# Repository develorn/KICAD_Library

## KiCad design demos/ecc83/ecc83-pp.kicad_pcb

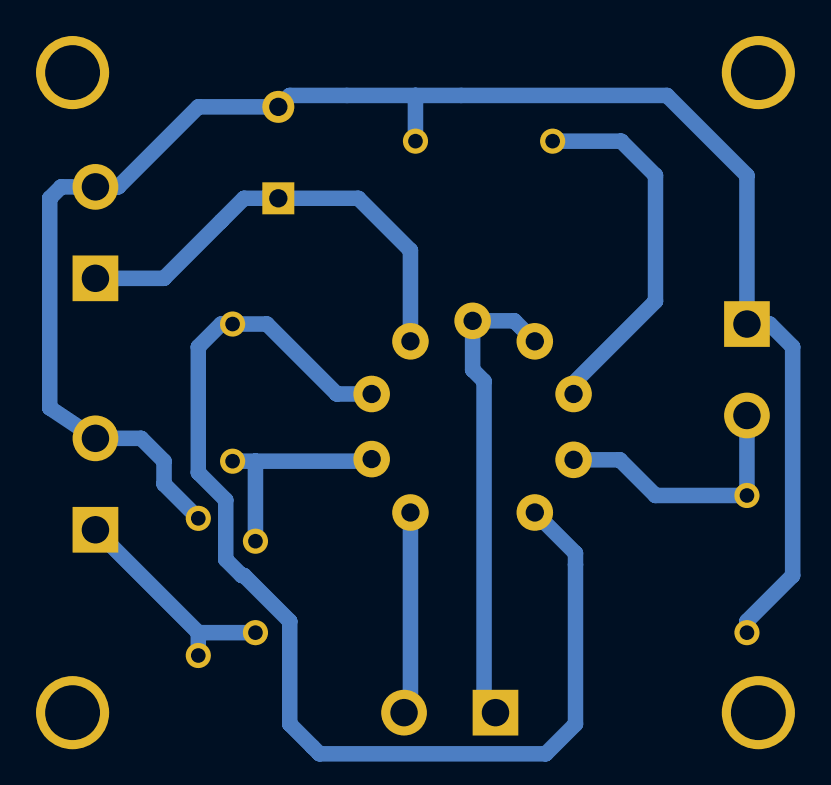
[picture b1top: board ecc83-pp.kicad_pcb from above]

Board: 2 copper layers, 15 parts (0 on the bottom side), 9 nets.

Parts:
1PIN, 1PIN#2, 1PIN#3, 1PIN#4: P***; 1pin
C1: 10uF; C2V10
C2: 680nF; C2
P1: IN; bornier2
P2: OUT; bornier2
P3: POWER; bornier2
P4: CONN_2; bornier2
R1, R2: 1.5K; R3
R3: 100K; R3
R4: 47K; R3
U1: ECC81_83; ECC-83-1

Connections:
GND: C1.2, P1.1, P2.2, P3.2, R2.2, R3.2, R4.2
unnamed: R1.1, U1.1, U1.7
unnamed: P4.2, U1.9
unnamed: P1.2, R4.1, U1.2
unnamed: R2.1, U1.3
unnamed: C2.1, P2.1, R3.1
unnamed: P4.1, U1.4, U1.5
unnamed: C1.1, P3.1, U1.6
unnamed: C2.2, R1.2, U1.8

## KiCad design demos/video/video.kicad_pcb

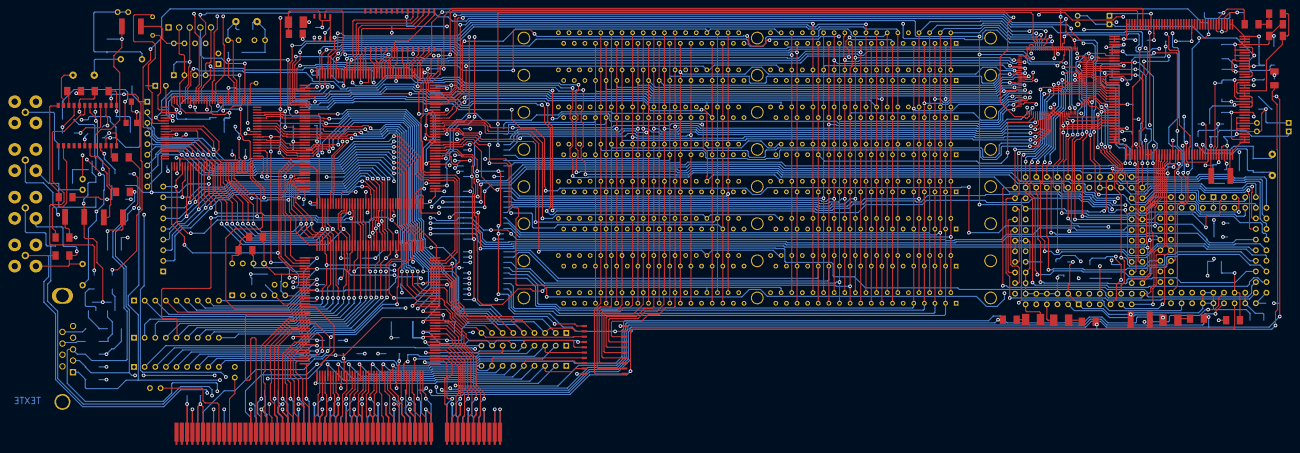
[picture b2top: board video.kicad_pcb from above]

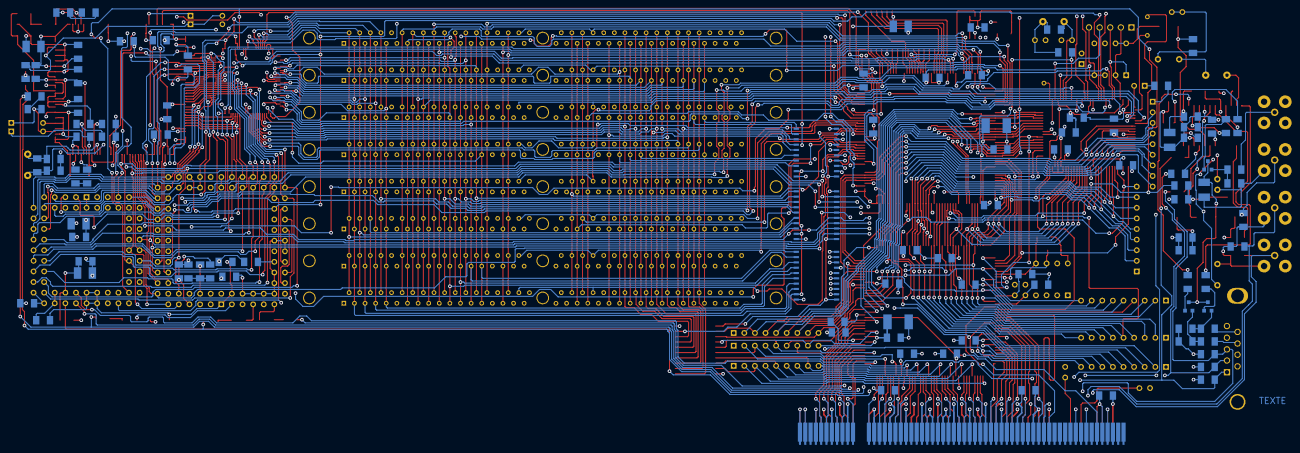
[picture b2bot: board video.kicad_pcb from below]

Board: 4 copper layers, 189 parts (103 on the bottom side), 371 nets.

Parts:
BUS1: BUSPCI_5V; BUSPCI
C1, C2, C3, C4, C5, C6, C7, C8, C9, C10, C11, C12, C13, C14, C15, C16, C17, C18, C19, C20, C21, C22, C23, C24, C25, C26, C27, C28, C29, C30, C31, C32, C33, C34, C35, C36, C70, C71, C72, C73: 100nF; SM1206
C37: 100pF; SM1206
C38, C56: 4,7uF; SM1812L
C39, C40, C41: 1uF; SM1210L
C42: 2,2uF; SM1210L
C43, C44, C45: 220nF; SM1206
C46, C47: 220pF; SM1206
C48: 22nF; SM1206
C49, C50: 22pF; C1
C51: 22uF; SM1210L
C52: 22uF; SM1206
C53: 330pF; SM1206
C54, C67, C68, C69: 4,7uF; SM1206
C55, C57: 4,7uF; SM1210L
C58, C59, C60, C61: 47nF; SM1206
C62, C63: 47uF; SM1210L
C64: 6,8uF; SM1210L
C65, C66: 22pF; SM1206
CV1: 5/30pF; CV3-30PF
D1, D2, D3, D4: BAT46; D3
D6: LED; LEDV
J4: DB9FEM; DB9FC
L1: 2,2uH; SM1812
L2, L3, L5: 22uH; SM1812
L4: 22uF; SM1812
L6: 470nS; LRTDK
P1, P2, P3, P8: BNC; SUBCLICK
P4: CONN_2; SIL-2
P5: CONN_5; PIN_ARRAY_5x1
P9, P10, P11: CONN_1; PINTST
P12: CONN_1; TESTPOINT
POT1: 100K; POT_CMS
Q1, Q2, Q3: BC848; SOT23EBC
R1: 10; SM1206
R2, R3: 100; SM1206
R4, R5, R6, R7, R48: 10K; SM1206
R8: 150; SM1206
R9: 150K; SM1206
R10, R11, R12, R13: 1K; SM1206
R14, R15: 1M; SM1206
R16, R17, R18, R19, R20, R21, R22, R23, R24: 220; SM1206
R25, R26: 220K; SM1206
R27: 27K; SM1206
R28, R29: 2,2K; SM1206
R30: 3,3K; SM1206
R31, R32, R33, R34, R35, R36: 470; SM1206
R37, R38: 510; SM1206
R39, R40, R41: 68; SM1206
R42, R43, R44, R45, R46, R47: 75; SM1206
RR1, RR2, RR3, RR6, RR8: 8x10K; SIL-9
RR4, RR5, RR7: 8x10K; r_pack8
U1: 24C16; 8dip300
U2: 4C4001; SO28
U3, U4, U5, U6: 74LS245; SO20L
U7: AV9173; SO8E
U8: BT253; PLCC84
U9: BT473; PLCC68
U10: BT812; PQFP160
U11: S5933_PQ160; PQFP160
U12, U13, U14, U15, U16, U17, U18, U19: SIM4X32; SIM72
U20: TDA8501; SO24E
U21: XC1736APD8; 8dip300
U22: XC4003-VQ100; VQFP100
U23: XC4003/PQ100; PQFP100
U24: XC4005-PQ160; PQFP160
W1: 16/32; SM1206
W2: FLOAT#; C1
W3: SERNV; C1
W4, W5: TEST; C1
X1: 10MHz; HC-18UV
X2: 30MHz; HC-18UV
X3: 4,433618MH; HC-18UH

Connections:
+3.3V: BUS1.A21, BUS1.A27, BUS1.A33, BUS1.A39, BUS1.A45, BUS1.A53, BUS1.B25, BUS1.B31, BUS1.B36, BUS1.B41, BUS1.B43, BUS1.B54, C68.1, C69.1
+5F: C55.1, L3.2, Q1.3, Q2.3, Q3.3
+5V: BUS1.A5, BUS1.A8, BUS1.A10, BUS1.A16, BUS1.A59, BUS1.A61, BUS1.A62, BUS1.B5, BUS1.B6, BUS1.B19, BUS1.B59, BUS1.B61, BUS1.B62, C9.1, C10.1, C11.1, C15.1, C17.1, C18.1, C19.1, C20.1, C21.1, C22.1, C24.1, C25.1, C26.1, C27.1, C28.1, C29.1, C30.1, C31.1, C38.1, C56.1, C57.1, C67.1, C70.1, C71.1, C72.1, C73.1, D2.2, D4.2, L2.1, L3.1, L4.1, L5.1, R1.2, R4.2, R5.2, R6.2, R7.2, R13.1, R28.1, R29.1, R48.1, RR1.1, RR2.1, RR3.1, RR4.1, RR5.1, RR6.1, RR7.1, RR8.1, U1.7, U1.8, U2.10, U3.20, U4.20, U5.20, U6.20, U10.31, U10.45, U10.57, U10.76, U10.91, U10.102, U10.112, U11.11, U11.31, U11.51, U11.71, U11.91, U11.111, U11.131, U11.151, U12.10, U12.30, U12.59, U13.10, U13.30, U13.59, U14.10, U14.30, U14.59, U15.10, U15.30, U15.59, U16.10, U16.30, U16.59, U17.10, U17.30, U17.59, U18.10, U18.30, U18.59, U19.10, U19.30, U19.59, U21.7, U21.8, U22.12, U22.22, U22.24, U22.25, U22.26, U22.37, U22.51, U22.63, U22.75, U22.89, U22.100, U23.3, U23.15, U23.28, U23.40, U23.54, U23.66, U23.78, U23.92, U24.20, U24.38, U24.40, U24.41, U24.42, U24.60, U24.81, U24.100, U24.120, U24.142, U24.160
/ESVIDEO-RVB/BLUE: C60.2, J4.3, R44.2, U9.39
/ESVIDEO-RVB/BLUE_IN: P3.1, R22.1, R46.1
/ESVIDEO-RVB/DPC0: RR7.2, U3.2, U8.16, U9.14, U10.92, U11.100, U23.13, U24.21
/ESVIDEO-RVB/DPC1: RR7.3, U3.3, U8.15, U9.15, U10.93, U11.99, U23.12, U24.22
/ESVIDEO-RVB/DPC2: RR7.4, U3.4, U8.14, U9.16, U10.94, U11.98, U23.11, U24.23
/ESVIDEO-RVB/DPC4: RR7.6, U3.6, U8.12, U9.18, U10.96, U11.95, U23.9, U24.25
/ESVIDEO-RVB/DPC5: RR7.7, U3.7, U8.11, U9.19, U10.97, U11.94, U23.8, U24.26
/ESVIDEO-RVB/DPC7: RR7.9, U3.9, U8.9, U9.21, U10.100, U11.88, U23.5, U24.28
/ESVIDEO-RVB/GREEN: C59.2, J4.2, R43.2, U9.38
/ESVIDEO-RVB/GREEN_IN: C3.2, P2.1, R23.1, R45.1
/ESVIDEO-RVB/OE_RVB-: U8.57, U9.29
/ESVIDEO-RVB/PCA0: U8.17, U9.24, U10.84, U23.65
/ESVIDEO-RVB/PCA2: U8.19, U9.26, U23.63
/ESVIDEO-RVB/RDCDA-: U9.22, U23.72
/ESVIDEO-RVB/REF+: R37.2, U8.64, U8.65, U8.66, U8.71, U8.73, U8.76, U8.78, U8.80, U8.82
/ESVIDEO-RVB/TVB2: U8.30, U9.63, U10.53, U22.94
/ESVIDEO-RVB/TVB3: U8.29, U9.64, U10.52, U22.95
/ESVIDEO-RVB/TVG0: U8.48, U9.53, U10.74, U22.67
/ESVIDEO-RVB/TVG1: U8.47, U9.54, U10.73, U22.68
/ESVIDEO-RVB/TVG2: U8.46, U9.55, U10.72, U22.69
/ESVIDEO-RVB/TVG3: U8.45, U9.56, U10.71, U22.70
/ESVIDEO-RVB/TVG4: U8.36, U9.57, U10.70, U22.71
/ESVIDEO-RVB/TVG5: U8.35, U9.58, U10.69, U22.78
/ESVIDEO-RVB/TVR0: U8.56, U9.45, U10.65, U22.82
/ESVIDEO-RVB/TVR1: U8.55, U9.46, U10.64, U22.83
/ESVIDEO-RVB/TVR2: U8.54, U9.47, U10.63, U22.84
/ESVIDEO-RVB/TVR5: U8.51, U9.50, U10.60, U22.87
/ESVIDEO-RVB/TVR6: U8.50, U9.51, U10.59, U22.90
/ESVIDEO-RVB/TVR7: U8.49, U9.52, U10.58, U22.91
/ESVIDEO-RVB/VAA: C33.1, C34.1, C35.1, C42.1, C51.1, C52.1, L5.2, U8.1, U8.43, U8.44, U8.84, U9.1, U9.2, U9.33, U9.34, U9.35, U9.36
/RAMS/CAS0-: U12.40, U13.40, U14.40, U15.40, U16.40, U17.40, U18.40, U19.40, U24.57
/RAMS/CAS2-: U12.42, U13.42, U14.42, U15.42, U16.42, U17.42, U18.42, U19.42, U24.59
/RAMS/CAS3-: U12.43, U13.43, U14.43, U15.43, U16.43, U17.43, U18.43, U19.43, U24.62
/RAMS/MXA0: U12.12, U13.12, U14.12, U15.12, U16.12, U17.12, U18.12, U19.12, U24.128
/RAMS/MXA1: U12.13, U13.13, U14.13, U15.13, U16.13, U17.13, U18.13, U19.13, U24.127
/RAMS/MXA2: U12.14, U13.14, U14.14, U15.14, U16.14, U17.14, U18.14, U19.14, U24.126
/RAMS/MXA3: U12.15, U13.15, U14.15, U15.15, U16.15, U17.15, U18.15, U19.15, U24.125
/RAMS/MXA4: U12.16, U13.16, U14.16, U15.16, U16.16, U17.16, U18.16, U19.16, U24.124
/RAMS/MXA5: U12.17, U13.17, U14.17, U15.17, U16.17, U17.17, U18.17, U19.17, U24.123
/RAMS/MXA6: U12.18, U13.18, U14.18, U15.18, U16.18, U17.18, U18.18, U19.18, U24.116
/RAMS/MXA7: U12.28, U13.28, U14.28, U15.28, U16.28, U17.28, U18.28, U19.28, U24.115
/RAMS/MXA8: U12.31, U13.31, U14.31, U15.31, U16.31, U17.31, U18.31, U19.31, U24.114
/RAMS/MXA9: U12.32, U13.32, U14.32, U15.32, U16.32, U17.32, U18.32, U19.32, U24.113
/RAMS/MXA10: U12.19, U13.19, U14.19, U15.19, U16.19, U17.19, U18.19, U19.19, U24.109
/RAMS/RAS3-: U15.34, U15.44, U24.68
/RAMS/RAS5-: U12.34, U12.44, U24.66
/RAMS/TVRAM0: U3.18, U12.2, U13.2, U14.2, U15.2, U16.2, U17.2, U18.2, U19.2, U22.17
/RAMS/TVRAM1: U3.17, U12.4, U13.4, U14.4, U15.4, U16.4, U17.4, U18.4, U19.4, U22.19
/RAMS/TVRAM2: U3.16, U12.6, U13.6, U14.6, U15.6, U16.6, U17.6, U18.6, U19.6, U22.20
/RAMS/TVRAM3: U3.15, U12.8, U13.8, U14.8, U15.8, U16.8, U17.8, U18.8, U19.8, U22.18
/RAMS/TVRAM4: U3.14, U12.20, U13.20, U14.20, U15.20, U16.20, U17.20, U18.20, U19.20, U22.28
/RAMS/TVRAM5: U3.13, U12.22, U13.22, U14.22, U15.22, U16.22, U17.22, U18.22, U19.22, U22.29
/RAMS/TVRAM6: U3.12, U12.24, U13.24, U14.24, U15.24, U16.24, U17.24, U18.24, U19.24, U22.31
/RAMS/TVRAM7: U3.11, U12.26, U13.26, U14.26, U15.26, U16.26, U17.26, U18.26, U19.26, U22.32
/RAMS/TVRAM8: U4.18, U12.49, U13.49, U14.49, U15.49, U16.49, U17.49, U18.49, U19.49, U22.33
/RAMS/TVRAM9: U4.17, U12.51, U13.51, U14.51, U15.51, U16.51, U17.51, U18.51, U19.51, U22.34
/RAMS/TVRAM10: U4.16, U12.53, U13.53, U14.53, U15.53, U16.53, U17.53, U18.53, U19.53, U22.35
/RAMS/TVRAM11: U4.15, U12.55, U13.55, U14.55, U15.55, U16.55, U17.55, U18.55, U19.55, U22.36
/RAMS/TVRAM12: U4.14, U12.57, U13.57, U14.57, U15.57, U16.57, U17.57, U18.57, U19.57, U22.39
/RAMS/TVRAM13: U4.13, U12.61, U13.61, U14.61, U15.61, U16.61, U17.61, U18.61, U19.61, U22.40
/RAMS/TVRAM14: U4.12, U12.63, U13.63, U14.63, U15.63, U16.63, U17.63, U18.63, U19.63, U22.41
/RAMS/TVRAM15: U4.11, U12.65, U13.65, U14.65, U15.65, U16.65, U17.65, U18.65, U19.65, U22.42
/RAMS/TVRAM16: U5.18, U12.3, U13.3, U14.3, U15.3, U16.3, U17.3, U18.3, U19.3, U22.43
/RAMS/TVRAM17: U5.17, U12.5, U13.5, U14.5, U15.5, U16.5, U17.5, U18.5, U19.5, U22.44
/RAMS/TVRAM18: U5.16, U12.7, U13.7, U14.7, U15.7, U16.7, U17.7, U18.7, U19.7, U22.45
/RAMS/TVRAM19: U5.15, U12.9, U13.9, U14.9, U15.9, U16.9, U17.9, U18.9, U19.9, U22.46
/RAMS/TVRAM20: U5.14, U12.21, U13.21, U14.21, U15.21, U16.21, U17.21, U18.21, U19.21, U22.47
/RAMS/TVRAM21: U5.13, U12.23, U13.23, U14.23, U15.23, U16.23, U17.23, U18.23, U19.23, U22.48
/RAMS/TVRAM22: U5.12, U12.25, U13.25, U14.25, U15.25, U16.25, U17.25, U18.25, U19.25, U22.53
/RAMS/TVRAM23: U5.11, U12.27, U13.27, U14.27, U15.27, U16.27, U17.27, U18.27, U19.27, U22.54
/RAMS/TVRAM24: U6.18, U12.50, U13.50, U14.50, U15.50, U16.50, U17.50, U18.50, U19.50, U22.55
/RAMS/TVRAM25: U6.17, U12.52, U13.52, U14.52, U15.52, U16.52, U17.52, U18.52, U19.52, U22.56
/RAMS/TVRAM26: U6.16, U12.54, U13.54, U14.54, U15.54, U16.54, U17.54, U18.54, U19.54, U22.57
/RAMS/TVRAM27: U6.15, U12.56, U13.56, U14.56, U15.56, U16.56, U17.56, U18.56, U19.56, U22.58
/RAMS/TVRAM28: U6.14, U12.58, U13.58, U14.58, U15.58, U16.58, U17.58, U18.58, U19.58, U22.59
/RAMS/TVRAM29: U6.13, U12.60, U13.60, U14.60, U15.60, U16.60, U17.60, U18.60, U19.60, U22.60
/RAMS/TVRAM30: U6.12, U12.62, U13.62, U14.62, U15.62, U16.62, U17.62, U18.62, U19.62, U22.61
/RAMS/TVRAM31: U6.11, U12.64, U13.64, U14.64, U15.64, U16.64, U17.64, U18.64, U19.64, U22.62
/RAMS/WRAM-: U12.47, U13.47, U14.47, U15.47, U16.47, U17.47, U18.47, U19.47, U24.63
/buspci.sch/ADR6: U11.132, U23.39, U24.143
/buspci.sch/BPCLK: U11.140, U23.30
/buspci.sch/EA1: RR2.6, U11.61
/buspci.sch/EA2: RR3.8, U11.69
/buspci.sch/EA3: RR3.6, U11.73
/buspci.sch/EA4: RR3.2, U11.81
/buspci.sch/EA5: RR4.4, U11.89
/buspci.sch/EA6: RR4.2, U11.97
/buspci.sch/EA7: RR5.9, U11.101
/buspci.sch/EA9: RR5.3, U11.113
/buspci.sch/EA10: RR6.9, U11.121
/buspci.sch/EA11: RR6.7, U11.129
/buspci.sch/EA12: RR6.5, U11.137
/buspci.sch/EA13: RR6.4, U11.141
/buspci.sch/EA14: RR4.8, U11.149
/buspci.sch/EA15: RR4.6, U11.153
/buspci.sch/EQ0: RR1.2, U11.1
/buspci.sch/EQ1: RR1.4, U11.9
/buspci.sch/EQ2: RR1.6, U11.17
/buspci.sch/EQ3: RR1.7, U11.21
/buspci.sch/EQ4: RR1.9, U11.29
/buspci.sch/EQ5: RR2.4, U11.33
/buspci.sch/EQ6: RR2.2, U11.41
/buspci.sch/EQ7: RR2.9, U11.49
/buspci.sch/PTATN-: RR5.2, U11.114, U23.18, U24.4
/buspci.sch/PTBE-1: U11.118, U23.21, U24.157
/buspci.sch/PTNUM0: U11.123, U23.34, U24.150
/buspci.sch/PTRDY-: RR6.2, U11.115, U23.19, U24.3
/buspci.sch/P_AD0: BUS1.A58, U11.56
/buspci.sch/P_AD1: BUS1.B58, U11.55
/buspci.sch/P_AD2: BUS1.A57, U11.54
/buspci.sch/P_AD3: BUS1.B56, U11.52
/buspci.sch/P_AD4: BUS1.A55, U11.48
/buspci.sch/P_AD5: BUS1.B55, U11.47
/buspci.sch/P_AD6: BUS1.A54, U11.46
/buspci.sch/P_AD7: BUS1.B53, U11.44
/buspci.sch/P_AD8: BUS1.B52, U11.42
/buspci.sch/P_AD9: BUS1.A49, U11.40
/buspci.sch/P_AD10: BUS1.B48, U11.39
/buspci.sch/P_AD11: BUS1.A47, U11.38
/buspci.sch/P_AD12: BUS1.B47, U11.36
/buspci.sch/P_AD13: BUS1.A46, U11.35
/buspci.sch/P_AD14: BUS1.B45, U11.34
/buspci.sch/P_AD15: BUS1.A44, U11.32
/buspci.sch/P_AD16: BUS1.A32, U11.14
/buspci.sch/P_AD17: BUS1.B32, U11.12
/buspci.sch/P_AD18: BUS1.A31, U11.8
/buspci.sch/P_AD19: BUS1.B30, U11.7
/buspci.sch/P_AD20: BUS1.A29, U11.6
/buspci.sch/P_AD21: BUS1.B29, U11.4
/buspci.sch/P_AD22: BUS1.A28, U11.3
/buspci.sch/P_AD23: BUS1.B27, U11.2
/buspci.sch/P_AD24: BUS1.A25, U11.158
/buspci.sch/P_AD25: BUS1.B24, U11.156
/buspci.sch/P_AD26: BUS1.A23, U11.155
/buspci.sch/P_AD27: BUS1.B23, U11.154
/buspci.sch/P_AD28: BUS1.A22, U11.152
/buspci.sch/P_AD29: BUS1.B21, U11.148
/buspci.sch/P_AD30: BUS1.A20, U11.147
/buspci.sch/P_AD31: BUS1.B20, U11.146
/buspci.sch/P_C/BE0#: BUS1.A52, U11.43
/buspci.sch/P_C/BE1#: BUS1.B44, U11.28
/buspci.sch/P_C/BE2#: BUS1.B33, U11.15
/buspci.sch/P_C/BE3#: BUS1.B26, U11.159
/buspci.sch/P_CLK: BUS1.B16, U11.142
/buspci.sch/P_DEVSEL#: BUS1.B37, U11.20
/buspci.sch/P_FRAME#: BUS1.A34, U11.16
/buspci.sch/P_GNT#: BUS1.A17, U11.143
/buspci.sch/P_IDSEL: BUS1.A26, U11.160
/buspci.sch/P_INTA#: BUS1.A6, U11.58
/buspci.sch/P_IRDY#: BUS1.B35, U11.18
/buspci.sch/P_LOCK#: BUS1.B39, U11.23
/buspci.sch/P_PAR: BUS1.A43, U11.27
/buspci.sch/P_PERR#: BUS1.B40, U11.24
/buspci.sch/P_REQ#: BUS1.B18, U11.144
/buspci.sch/P_RST#: BUS1.A15, U11.139
/buspci.sch/P_SERR#: BUS1.B42, U11.26
/buspci.sch/P_STOP#: BUS1.A38, U11.22
/buspci.sch/P_TRDY#: BUS1.A36, U11.19
/buspci.sch/RDFIFO-: RR5.7, U11.104, U24.16
/buspci.sch/WRFIFO-: RR5.8, U11.102, U24.18
/buspci.sch/WRFULL: U11.103, U24.17
/buspci.sch/X_IRQ: RR5.4, U11.109, U24.11
/graphic/14MHZOUT: U7.6, U24.95
/graphic/ADR2: U11.68, U23.48, U24.137
/graphic/ADR3: U11.67, U23.44, U24.138
/graphic/ADR4: U11.66, U23.43, U24.139
/graphic/ADR5: U11.64, U23.42, U24.140
/graphic/BE-0: U11.87, U23.38, U24.144
/graphic/BE-1: U11.63, U23.37, U24.145
/graphic/BE-2: U11.62, U23.36, U24.146
/graphic/BE-3: U11.60, U23.35, U24.147
/graphic/BLANK-: U9.7, U22.8, U24.53
/graphic/BT812_RD-: U10.86, U23.71
/graphic/BT812_WR-: U10.83, U23.70
/graphic/CADCLK: U8.38, U8.39, U8.40, U22.2, U24.77
/graphic/CAS1-: U12.41, U13.41, U14.41, U15.41, U16.41, U17.41, U18.41, U19.41, U24.58
/graphic/CCLK: P5.2, U21.2, U23.77
/graphic/CDACLK: U9.9, U22.79, U24.76
/graphic/CLAMP: U8.37, U8.59, U22.7, U24.75
/graphic/CLK10MHz: R21.2, U23.57, U24.2
/graphic/CSIO-: U23.61, U24.159
/graphic/CSYNCIN-: U8.8, U24.54
/graphic/DIN: P5.3, U21.1, U23.75
/graphic/DONE: P5.4, U23.53
/graphic/HDOUT: U7.1, U24.7
/graphic/HDREFOUT: U7.2, U24.6
/graphic/IA0: U2.6, U24.94
/graphic/IA1: U2.7, U24.92
/graphic/IA2: U2.8, U24.88
/graphic/IA3: U2.9, U24.87
/graphic/IA4: U2.11, U24.86
/graphic/IA5: U2.12, U24.85
/graphic/IA6: U2.13, U24.83
/graphic/IA7: U2.14, U24.78
/graphic/IA8: U2.15, U24.93
/graphic/IA9: U2.5, U24.96
/graphic/ICAS-: U2.17, U24.104
/graphic/ID0: U2.1, U24.102
/graphic/ID1: U2.2, U24.99
/graphic/ID2: U2.18, U24.105
/graphic/ID3: U2.19, U24.106
/graphic/IOE-: U2.16, U24.103
/graphic/IRAS-: U2.4, U24.97
/graphic/IRQ-: U11.124, U24.149
/graphic/IRQ_SLR: RR2.7, U11.57, U24.134
/graphic/IWR-: U2.3, U24.98
/graphic/LED: D6.2, U23.81
/graphic/PCA1: U8.18, U9.25, U10.85, U23.64
/graphic/PROG*: P5.5, U21.3, U21.4, U23.55
/graphic/PTADR-: RR5.5, U11.107, U23.24, U24.14
/graphic/PTBE-0: U11.116, U23.20, U24.158
/graphic/PTBE-2: U11.119, U23.22, U24.156
/graphic/PTBE-3: U11.120, U23.23, U24.155
/graphic/PTBURST-: U11.112, U23.17, U24.5
/graphic/PTNUM1: U11.122, U23.32, U24.154
/graphic/PTWR: U11.108, U23.16, U24.12
/graphic/RAS0-: U19.34, U19.44, U24.74
/graphic/RAS1-: U18.34, U18.44, U24.73
/graphic/RAS2-: U17.34, U17.44, U24.69
/graphic/RAS4-: U16.34, U16.44, U24.67
/graphic/RAS6-: U14.34, U14.44, U24.65
/graphic/RAS7-: U13.34, U13.44, U24.64
/graphic/RD-: RR3.7, U11.72, U23.46, U24.133
/graphic/RDCAD-: U8.20, U23.74
/graphic/RDEMPTY: U11.106, U24.15
/graphic/RESERV1: U23.59, U24.44
/graphic/SELECT-: RR3.4, U11.75, U23.45, U24.135
/graphic/TVI0: U9.10, U24.108
/graphic/TVI1: U9.11, U24.107
/graphic/VOSC: C23.1, C63.1, R1.1, U7.4, U7.5, U7.7
/graphic/WR-: RR3.5, U11.74, U23.47, U24.132
/graphic/WRCAD-: U8.24, U23.69
/graphic/WRCDA-: U9.23, U23.73
/graphic/XTAL_I: C50.1, R26.1, U23.56, X1.2
/graphic/X_CLK: U22.74, U23.86, U24.119
/graphic/X_DIN: U23.85, U24.117
/graphic/X_PROG-: U22.52, U23.84, U24.82
/modul/BLEU: C58.2, J4.1, R42.2, U9.37
/modul/CHROM: R16.2, U20.14
/modul/COUT: J4.8, R39.1
/modul/CSYNC-OUT: R30.2, U9.8, U22.9, U24.13
/modul/CVBS: R18.2, U20.16
/modul/CVBSOUT: P8.1, R41.1
/modul/LUM: R17.2, U20.19
/modul/YOUT: J4.9, R40.2
/muxdata/ACCES_RAM-: U3.19, U4.19, U5.19, U6.19, U22.21, U24.56
/muxdata/ACQ_ON: U22.13, U24.48
/muxdata/DATA_WR: U3.1, U4.1, U5.1, U6.1, U24.55
/muxdata/DPC3: RR7.5, U3.5, U8.13, U9.17, U10.95, U11.96, U23.7, U24.24
/muxdata/DPC6: RR7.8, U3.8, U8.10, U9.20, U10.99, U11.92, U23.6, U24.27
/muxdata/DPC8: RR8.9, U4.2, U11.86, U23.97, U24.32
/muxdata/DPC9: RR8.8, U4.3, U11.84, U23.96, U24.33
/muxdata/DPC10: RR8.7, U4.4, U11.83, U23.95, U24.34
/muxdata/DPC11: RR8.6, U4.5, U11.82, U23.94, U24.35
/muxdata/DPC12: RR8.5, U4.6, U11.80, U23.93, U24.36
/muxdata/DPC13: RR8.4, U4.7, U11.79, U23.90, U24.45
/muxdata/DPC14: RR8.3, U4.8, U11.78, U23.88, U24.46
/muxdata/DPC15: RR8.2, U4.9, U11.76, U23.89, U24.47
/muxdata/DPC16: RR4.7, U5.2, U11.157
/muxdata/DPC17: RR4.9, U5.3, U11.145
/muxdata/DPC18: RR6.6, U5.4, U11.133
/muxdata/DPC19: RR6.8, U5.5, U11.125
/muxdata/DPC20: RR6.3, U5.6, U11.117
/muxdata/DPC21: RR5.6, U5.7, U11.105
/muxdata/DPC22: RR4.3, U5.8, U11.93
/muxdata/DPC23: RR4.5, U5.9, U11.85
/muxdata/DPC24: RR3.3, U6.2, U11.77
/muxdata/DPC25: RR3.9, U6.3, U11.65
/muxdata/DPC26: RR2.8, U6.4, U11.53
/muxdata/DPC27: RR2.5, U6.5, U11.45
/muxdata/DPC28: RR2.3, U6.6, U11.37
/muxdata/DPC29: RR1.8, U6.7, U11.25
/muxdata/DPC30: RR1.5, U6.8, U11.13
/muxdata/DPC31: RR1.3, U6.9, U11.5
/muxdata/TVB0: U8.32, U9.61, U10.55, U22.92
/muxdata/TVB1: U8.31, U9.62, U10.54, U22.93
/muxdata/TVB4: U8.28, U9.65, U10.51, U22.96
/muxdata/TVG6: U8.34, U9.59, U10.68, U22.80
/muxdata/TVG7: U8.33, U9.60, U10.67, U22.81
/muxdata/X_DIN: U22.72, U24.118
/muxdata/X_DONE: U22.50, U23.83, U24.80
/pal-ntsc.sch/C-VIDEO: D3.2, D4.1, R2.1, U10.125
/pal-ntsc.sch/F_PALIN: U10.104, U24.43
/pal-ntsc.sch/HD_PAL-: U10.36, U24.52
/pal-ntsc.sch/OE_PAL-: U9.28, U10.46, U10.47
/pal-ntsc.sch/RED_IN: C4.2, P1.1, R24.1, R47.1
/pal-ntsc.sch/RESET-: U10.87, U11.126, U23.1, U24.148
/pal-ntsc.sch/TVB5: U8.27, U9.66, U10.50, U22.97
/pal-ntsc.sch/TVB6: U8.26, U9.67, U10.49, U22.98
/pal-ntsc.sch/TVB7: U8.25, U9.68, U10.48, U22.99
/pal-ntsc.sch/TVR3: U8.53, U9.48, U10.62, U22.85
/pal-ntsc.sch/TVR4: U8.52, U9.49, U10.61, U22.86
/pal-ntsc.sch/VAF: C2.1, C12.1, C13.1, C14.1, C62.1, L4.2, R12.2, U10.1, U10.2, U10.39, U10.40, U10.41, U10.42, U10.43, U10.78, U10.79, U10.80, U10.81, U10.82, U10.119, U10.120, U10.121, U10.122, U10.123, U10.132, U10.141, U10.142, U10.149, U10.158, U10.159, U10.160
/pal-ntsc.sch/VD_PAL-: U10.34, U24.37
/pal-ntsc.sch/Y-VIDEO: D1.2, D2.1, R3.1, U10.156
/pal-ntsc.sch/Y_SYNC: R20.2, R35.2, U10.6
GND: BUS1.A18, BUS1.A24, BUS1.A30, BUS1.A35, BUS1.A37, BUS1.A42, BUS1.A48, BUS1.A56, BUS1.B3, BUS1.B15, BUS1.B17, BUS1.B22, BUS1.B28, BUS1.B34, BUS1.B38, BUS1.B46, BUS1.B49, BUS1.B57, C2.2, C6.2, C7.2, C9.2, C10.2, C11.2, C12.2, C13.2, C14.2, C15.2, C16.2, C17.2, C18.2, C19.2, C20.2, C21.2, C22.2, C23.2, C24.2, C25.2, C26.2, C27.2, C28.2, C29.2, C30.2, C31.2, C32.1, C33.2, C37.1, C38.2, C43.2, C44.2, C45.2, C46.2, C47.2, C48.1, C49.2, C50.2, C51.2, C52.2, C53.2, C54.2, C55.2, C56.2, C57.2, C62.2, C63.2, C64.2, C65.1, C66.1, C67.2, C68.2, C69.2, C70.2, C71.2, C72.2, C73.2, CV1.2, D1.1, D3.1, J4.4, J4.5, J4.6, J4.7, L6.3, P1.2, P2.2, P3.2, P4.2, P5.1, P8.2, P12.1, POT1.2, POT1.3, R8.2, R14.2, R15.1, R31.1, R32.2, R33.2, R34.2, R37.1, R38.2, R42.1, R43.1, R44.1, R45.2, R46.2, R47.2, U1.1, U1.2, U1.3, U1.4, U2.20, U3.10, U4.10, U5.10, U6.10, U7.3, U8.2, U8.3, U8.21, U8.22, U8.23, U8.41, U8.42, U8.61, U8.63, U8.67, U9.3, U9.4, U9.12, U9.13, U9.31, U9.32, U10.3, U10.5, U10.7, U10.16, U10.30, U10.44, U10.56, U10.66, U10.75, U10.88, U10.89, U10.90, U10.98, U10.103, U10.111, U10.116, U10.118, U10.124, U10.126, U10.128, U10.130, U10.134, U10.136, U10.138, U10.139, U10.143, U10.145, U10.147, U10.151, U10.153, U10.155, U10.157, U11.10, U11.30, U11.50, U11.70, U11.90, U11.110, U11.130, U11.150, U12.1, U12.39, U12.72, U13.1, U13.39, U13.72, U14.1, U14.39, U14.72, U15.1, U15.39, U15.72, U16.1, U16.39, U16.72, U17.1, U17.39, U17.72, U18.1, U18.39, U18.72, U19.1, U19.39, U19.72, U20.10, U20.17, U21.5, U22.1, U22.11, U22.23, U22.38, U22.49, U22.64, U22.77, U22.88, U23.4, U23.14, U23.26, U23.41, U23.52, U23.67, U23.80, U23.91, U24.1, U24.10, U24.19, U24.29, U24.39, U24.51, U24.61, U24.70, U24.79, U24.91, U24.101, U24.110, U24.122, U24.131, U24.141, U24.151, W1.1, W2.1, W3.1, W4.1, W5.1
unnamed: C54.1, L2.2, U20.8
unnamed: Q2.2, R17.1
unnamed: Q3.2, R18.1
unnamed: Q1.1, R32.1, R39.2
unnamed: L6.1, R10.1
unnamed: R10.2, U20.22
unnamed: C61.1, R30.1, R31.2
unnamed: Q3.1, R34.1, R41.2
unnamed: POT1.1, R9.1
unnamed: C48.2, C64.1, R11.2, U20.13
unnamed: Q2.1, R33.1, R40.1
unnamed: Q1.2, R16.1
unnamed: L6.2, R11.1, U20.20
unnamed: R9.2, U20.21
unnamed: U20.23, X3.2
unnamed: C45.1, U20.15
unnamed: L1.1, U20.18
unnamed: C46.1, C53.1, L1.2
unnamed: C59.1, U20.9
unnamed: C58.1, U20.11
unnamed: C61.2, U20.24
unnamed: C43.1, U20.12
unnamed: CV1.1, X3.1
unnamed: R4.1, U20.2
unnamed: C44.1, U20.6
unnamed: C60.1, U20.7
unnamed: C7.1, R27.2, U10.114
unnamed: C1.1, C47.1, R35.1
unnamed: C6.1, R12.1, U10.113, U10.137, U10.144
unnamed: C16.1, U10.110
unnamed: C66.2, R25.1, U10.108, X2.2
unnamed: C65.2, R25.2, U10.109, X2.1
unnamed: C1.2, R14.1, U10.140
unnamed: C5.1, U10.117
unnamed: C8.1, U10.4
unnamed: C4.1, R2.2
unnamed: C3.1, R3.2
unnamed: C8.2, R20.1
unnamed: R19.2, U10.115
unnamed: C5.2, R19.1
unnamed: R27.1, U10.135
unnamed: D6.1, R13.2
unnamed: C49.1, R21.1, R26.2, X1.1
unnamed: P10.1, U23.87
unnamed: P11.1, U23.82
unnamed: P9.1, U23.51
unnamed: P4.1, R48.2, U23.25, U23.27, U23.29
unnamed: R7.1, U11.135, W3.2
unnamed: R6.1, U11.138, W2.2
unnamed: R5.1, U11.59, W1.2
unnamed: R29.2, U1.5, U11.127
unnamed: R28.2, U1.6, U11.128
unnamed: BUS1.A4, BUS1.B4
unnamed: BUS1.B11, W4.2
unnamed: BUS1.B9, W5.2
unnamed: C39.1, U8.83
unnamed: C36.1, R15.2, U8.7
unnamed: C36.2, C37.2, R36.1
unnamed: C41.1, U8.75
unnamed: C41.2, R22.2
unnamed: C40.1, U8.79
unnamed: C40.2, R23.2
unnamed: C39.2, R24.2
unnamed: U8.58, U8.68
unnamed: U8.60, U8.70
unnamed: U8.62, U8.72
unnamed: R38.1, U8.69
unnamed: R36.2, U8.6
unnamed: C32.2, U9.43, U9.44
unnamed: C35.2, U9.41, U9.42
unnamed: C34.2, C42.2, R8.1, U9.40

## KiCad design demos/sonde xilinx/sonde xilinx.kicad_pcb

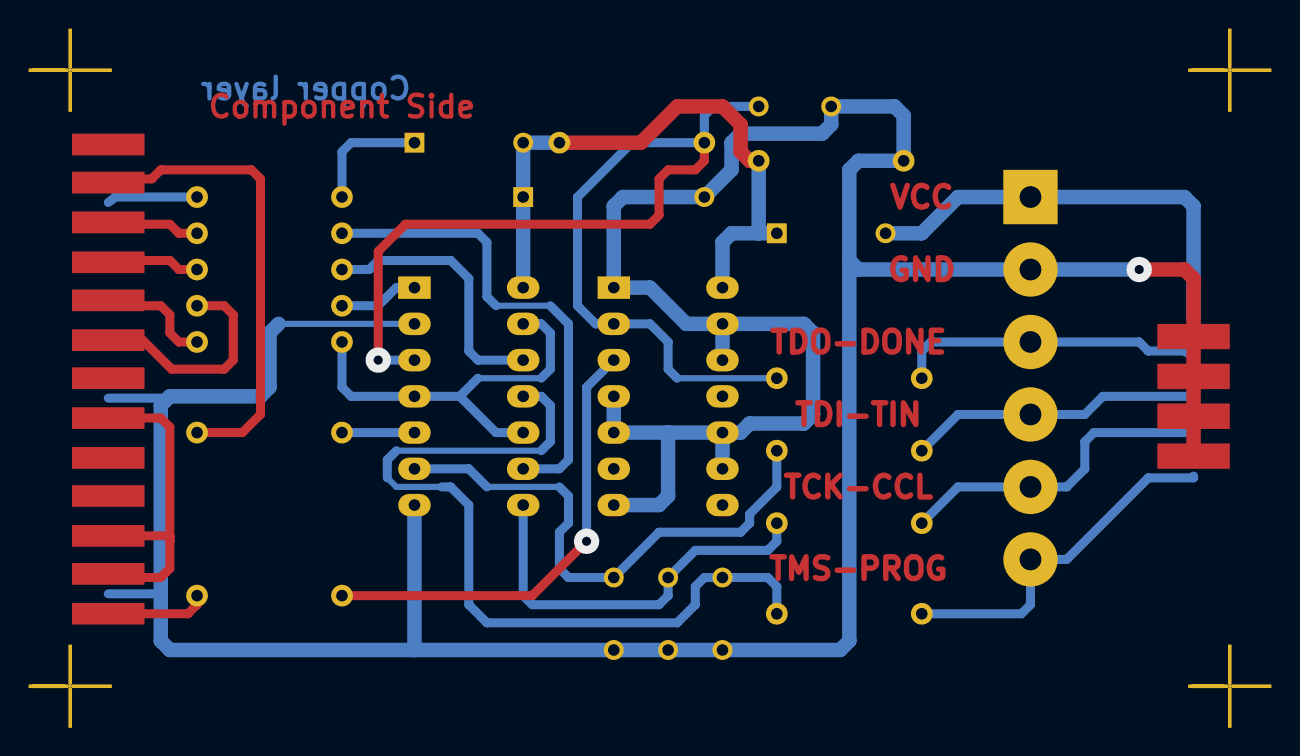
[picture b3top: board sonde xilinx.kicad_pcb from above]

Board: 2 copper layers, 29 parts (0 on the bottom side), 26 nets.

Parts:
C1: 1uF; CP5
C2, C3, C4, C5: 100pF; C2
D1, D2: BAT46; D3
J1: DB25MALE; DB25M_CI
J2: DB9MALE; DB9M_CI_INVERT
MIRE: *; MIRE
MIRE#2, MIRE#3, MIRE#4: *; MIRE
P1: CONN_6; bornier6
R1, R6, R7, R8, R9, R10, R11, R12, R13, R14: 100; R4
R2: 5,1K; R4
R4: 47; R4
R5: 1K; R4
U1, U2: 74LS125; 14DIP-ELL300

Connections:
/CLK-D1: J1.3, R10.2
/CTRL-D3: J1.5, R8.2
/DONE-SELECT*: J1.13, R4.2
/PWR_3,3-5V: D2.1, J2.1, P1.1
/TCK-CCLK: J2.4, P1.5, R12.1
/TD0-DONE: J2.2, P1.3, R14.1
/TD0-PROG-D4: J1.6, R6.2
/TDI-DIN: J2.3, P1.4, R11.1
/TDI-DIN-D0: J1.2, R7.2
/TMS-PROG: J2.5, P1.6, R13.1
/TMS-PROG-D2: J1.4, R9.2
/VCC_SENSE-ERROR*: J1.15, R1.2
GND: C1.2, C2.2, C3.2, C4.2, C5.2, J1.20, J1.25, J2.6, J2.7, J2.8, J2.9, P1.2, R5.2, U1.2, U1.7, U2.1, U2.4, U2.5, U2.7, U2.9, U2.10, U2.12, U2.13
unnamed: J1.8, J1.11, J1.12
unnamed: D1.2, R1.1
unnamed: R4.1, U2.3
unnamed: R7.1, U1.5
unnamed: R10.1, U1.9
unnamed: R6.1, U1.1
unnamed: R9.1, U1.12
unnamed: R8.1, U1.4, U1.10, U1.13
unnamed: C4.1, R13.2, U1.11
unnamed: C2.1, R11.2, U1.6
unnamed: C5.1, R12.2, U1.8
unnamed: C3.1, R2.2, R14.2, U1.3, U2.2
VCC: C1.1, D1.1, D2.2, R2.1, R5.1, U1.14, U2.14

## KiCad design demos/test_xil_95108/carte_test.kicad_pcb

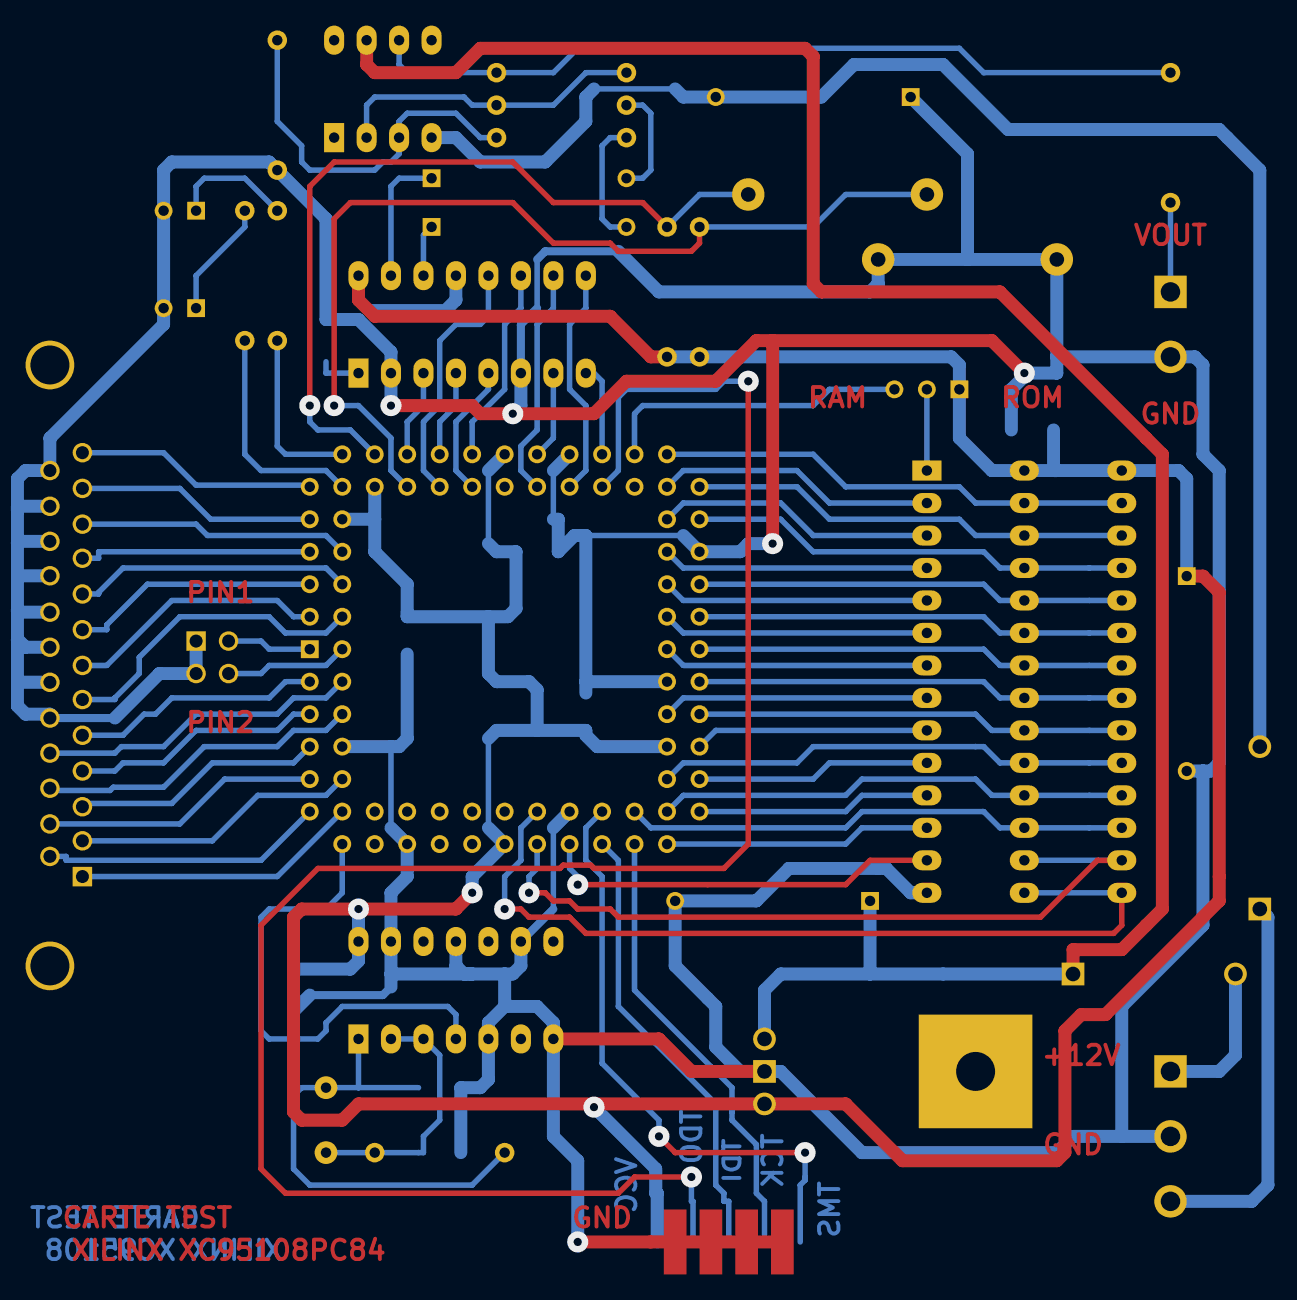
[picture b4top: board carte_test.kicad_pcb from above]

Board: 2 copper layers, 42 parts (0 on the bottom side), 83 nets.

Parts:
C1, C7, C8, C10, C11, C12: 100nF; SM1206
C2, C3, C13, C14: 10uF; CP6
C4, C5: 22pF; SM1206
C6: 47uF; CP6
D1, D4: 1N4004; D5
D2, D3: LED; LEDV
J1: DB25; DB25FC
J2: DB9FEM; DB9F_CI_INVERT
K1: CONN_3; SIL-3
P2: CONN_3; bornier3
P3: CONN_2; bornier2
P4: CONN_2X2; head_2x2
R1: 100K; R4
R2, R3: 330; R4
R4, R5: 4,7K; R4
R6: 1,1k; R4
R7: 1,1K; R4
R8, R9: 2,2K; R4
R10: 75; R4
SW1, SW2: SW_PUSH
U1: TDA8702; 16DIP-ELL300
U2: XC95108PC84; PLCC84
U3: LM7805; LM78XX
U4: 74HC04; 14DIP-ELL300
U5: RAM_32KO; 28DIP-ELL300-600
U6: LM318N; 8DIP-ELL300
X1: 10MHz; HC-18UH

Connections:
+12V: C6.1, D1.2, U3.VI, U6.7
-12V: C13.2, D4.1, U6.4
CSMEM_1: U2.39, U5.20
DAT0_1: U1.12, U2.69
DAT1_1: U1.11, U2.66
DAT2_1: U1.3, U2.70
DAT3_1: U1.4, U2.68
DAT4_1: U1.10, U2.63
DAT5_1: U1.9, U2.61
DAT6_1: U1.8, U2.58
DAT7_1: U1.7, U2.62
DCLK_1: U1.5, U2.67
GND: C1.2, C3.2, C4.2, C5.2, C6.2, C7.2, C8.2, C10.2, C11.2, C12.2, C13.1, D2.2, D3.2, J1.18, J1.19, J1.20, J1.21, J1.22, J1.23, J1.24, J1.25, J2.6, J2.7, J2.8, J2.9, P2.2, P3.2, P4.1, P4.3, R6.2, SW1.2, SW2.2, U1.2, U1.6, U2.8, U2.16, U2.27, U2.42, U2.49, U2.60, U3.GND, U4.5, U4.7, U4.9, U4.11, U4.13, U5.14
LED1_1: R2.2, U2.76
LED2_1: R3.2, U2.74
MA0_1: U2.33, U5.11
MA1_1: U2.32, U5.12
MA2_1: U2.26, U5.13
MA3_1: U2.25, U5.15
MA4_1: U2.24, U5.16
MA5_1: U2.31, U5.17
MA6_1: U2.34, U5.18
MA7_1: U2.36, U5.19
MD0_1: U2.35, U5.10
MD1_1: U2.37, U5.9
MD2_1: U2.40, U5.8
MD3_1: U2.44, U5.7
MD4_1: U2.46, U5.6
MD5_1: U2.48, U5.5
MD6_1: U2.50, U5.4
MD7_1: U2.52, U5.3
MD8_1: U2.51, U5.25
MD9_1: U2.47, U5.24
MD10_1: U2.41, U5.21
MD11_1: U2.45, U5.23
MD12_1: U2.55, U5.2
MD13_1: U2.53, U5.26
MD14_1: K1.3, U2.56
unnamed: D4.2, P2.3
unnamed: D1.1, P2.1
unnamed: R6.1, R9.1, U6.3
unnamed: R7.1, R10.2, U6.6
unnamed: R7.2, R8.1, U6.2
unnamed: C14.2, R8.2
unnamed: P3.1, R10.1
unnamed: C2.2, R9.2
unnamed: C14.1, U1.15
unnamed: D3.1, R3.1
unnamed: D2.1, R2.1
unnamed: K1.2, U5.1
unnamed: C4.1, R1.1, U4.2, U4.3, X1.2
unnamed: C5.1, R1.2, U4.1, X1.1
unnamed: C2.1, U1.14
unnamed: C1.1, U1.1
OEMEM_1: U2.43, U5.22
PARBUS0_1: J1.2, U2.10
PARBUS1_1: J1.3, U2.7
PARBUS2_1: J1.4, U2.5
PARBUS3_1: J1.5, U2.3
PARBUS4_1: J1.6, U2.84
PARBUS5_1: J1.7, U2.83
PARBUS6_1: J1.8, U2.81
PARBUS7_1: J1.9, U2.82
PAR_AUX0_X00001: J1.1, U2.13
PAR_AUX1_X00004: J1.15, U2.9
PAR_AUX2_X00003: J1.14, U2.11
PAR_AUX3_X00002: J1.13, U2.75
PAR_AUX4/PE_1: J1.12, U2.77
PAR_AUX5/BUSY*_1: J1.11, U2.80
PAR_AUX6/ACK_1: J1.10, U2.79
PAR_AUX7/INIT_1: J1.16, U2.6
PAR_AUX8_X00005: J1.17, U2.4
PIN_TEST0_1: P4.2, U2.1
PIN_TEST1_1: P4.4, U2.2
R/W-A14_1: U2.54, U5.27
SW0_1: R5.2, SW1.1, U2.72
SW1_1: R4.2, SW2.1, U2.71
TCK_1: J2.4, U2.30
TDI_1: J2.3, U2.28
TDO_1: J2.2, U2.59
TMS_1: J2.5, U2.29
VCC: C3.1, C7.1, C8.1, C10.1, C11.1, C12.1, J2.1, K1.1, R4.1, R5.1, U1.13, U1.16, U2.22, U2.38, U2.64, U2.73, U2.78, U3.VO, U4.14, U5.28
XIN/CLK_1: U2.12, U4.4
